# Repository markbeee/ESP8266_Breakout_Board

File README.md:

# **Breakout board for ESP8266 modules ESP-12 and ESP-07**
 
The single sided self etchable pcb is designed to power the ESP-module, has a reset and flash (program) button, the necessary pull-up/ pull-down resistors and a USB-to-serial IC (CH340G) to connect the adapter board via micro USB to the USB port on a PC. You can also wire a serial connection directly to the RX/ TX module pins.

Please bear in mind that the module pins have a 3.3 volt signal level. If you use a signal source with 5 volt (e.g. an Arduino driven by 5 volt) the RX-pin has to be driven by a voltage divider or any kind of level shifter.

The module can be connected to a power source via USB, the Vcc-pin of the module (max. 3.6 volt) or via the Vin-pins (max. 12 volt, min. 4.8 volt).

You can also connect the RTS and DTR lines via the solder bridges. If you do, you can automatically flash the module without any hassle pressing buttons. Unfortunately there are some issues with the serial output with the Arduino IDE then.

The adapter can be placed on any breadboard and leaves one row on each side available to put in jumper wires.

As the pcb is single sided you have to connect three jumper wires on the bottom (see Eagle-files for directions).

#### Parts needed (SMD)

| Part | Device                    | Value |
|------|---------------------------|-------|
| C1   | C-EUC0805                 | 22pF  |
| C2   | C-EUC0805                 | 22pF  |
| C3   | C-EUC0805                 | 100nF |
| C4   | C-EUC1206                 | 10µF  |
| C5   | C-EUC1206                 | 10µF  |
| IC1  | REG1117                   |       |
| JP1  | PINHD-1X8BIG              |       |
| JP2  | PINHD-1X8BIG              |       |
| JP3  | USB_MICROB_PLUGCONN-11752 |       |
| Q1   | CRYSTALHC49UP             | 12MHz |
| R1   | R-EU_M0805                | 4k7   |
| R2   | R-EU_M0805                | 4k7   |
| R3   | R-EU_M0805                | 4k7   |
| R4   | R-EU_M0805                | 4k7   |
| R5   | R-EU_M0805                | 1k    |
| R6   | R-EU_M0805                | 1k    |
| SJ1  | SJ                        |       |
| SJ2  | SJ                        |       |
| U$1  | ESP8266_ESP-12/ ESP-07    |       |
| U$2  | CH340G                    |       |
| U$3  | TACTILE-SWITCH-7914G      |       |
| U$4  | TACTILE-SWITCH-7914G      |       |

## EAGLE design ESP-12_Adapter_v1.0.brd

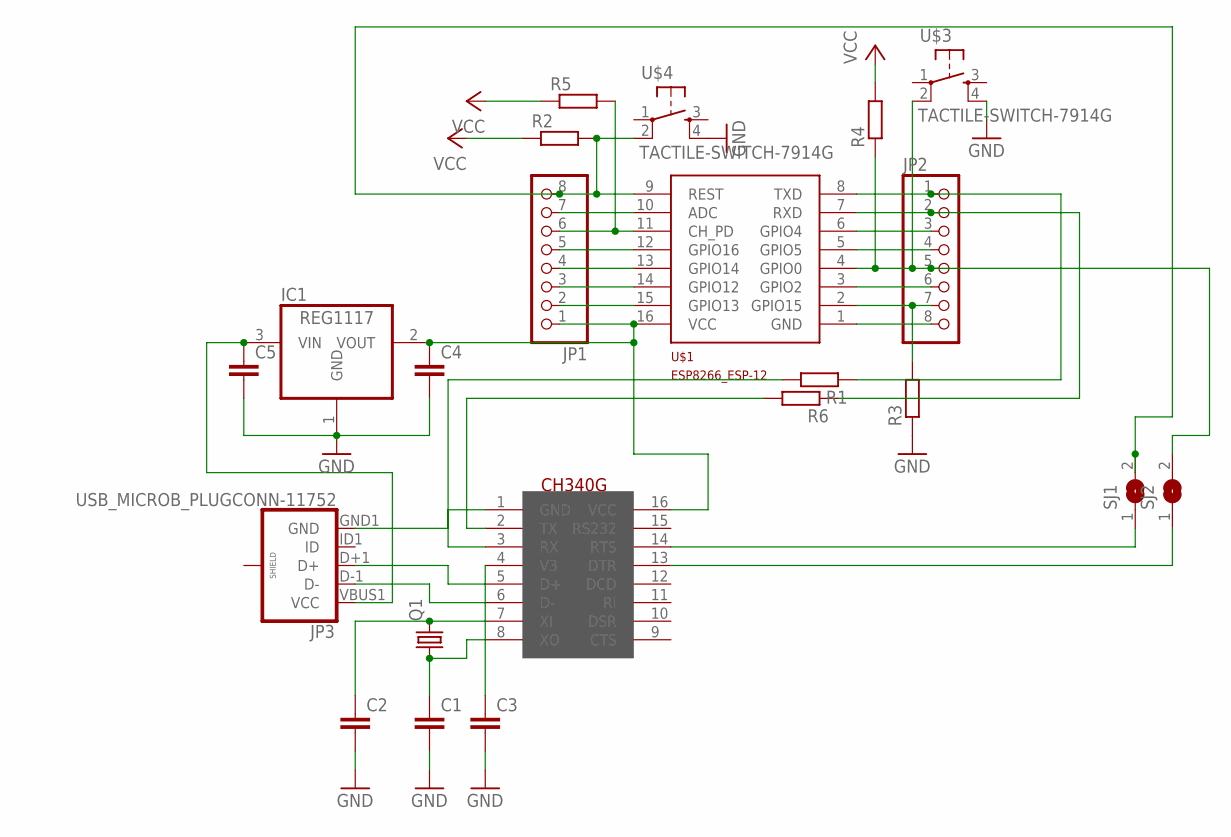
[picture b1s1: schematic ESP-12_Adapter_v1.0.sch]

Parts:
C1, C2, C3: C-EUC0805; C0805
C4, C5: C-EUC1206; C1206
IC1: REG1117; SOT223
JP1, JP2: PINHD-1X8BIG; 1X08-BIG
JP3: USB_MICROB_PLUGCONN-11752; USB-B-MICRO-SMD_V03
Q1: CRYSTALHC49UP; HC49UP
R1, R2, R3, R4, R5, R6: R-EU_M0805; M0805
SJ1, SJ2: SJ
U$1: ESP8266_ESP-12; ESP8266-ESP12
U$2: CH340G; SOIC16
U$3, U$4: TACTILE-SWITCH-7914G; 7914G

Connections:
GND: C1.2, C2.2, C3.2, C4.2, C5.2, IC1.1 (GND), JP2.8, JP3.GND1 (GND), R3.1, U$1.1 (GND), U$2.1 (GND), U$3.4, U$4.4
unnamed: JP1.8, R2.2, SJ1.2, U$1.9 (REST), U$4.2
unnamed: JP1.7, U$1.10 (ADC)
unnamed: C5.1, IC1.3 (VIN), JP3.VBUS1 (VCC)
unnamed: JP1.5, U$1.12 (GPIO16)
unnamed: JP1.4, U$1.13 (GPIO14)
unnamed: JP1.3, U$1.14 (GPIO12)
unnamed: JP1.2, U$1.15 (GPIO13)
unnamed: JP3.D+1 (D+), U$2.5 (D+)
unnamed: JP3.D-1 (D-), U$2.6 (D-)
unnamed: JP2.7, R3.2, U$1.2 (GPIO15)
unnamed: JP2.6, U$1.3 (GPIO2)
unnamed: JP2.4, U$1.5 (GPIO5)
unnamed: JP2.3, U$1.6 (GPIO4)
unnamed: JP2.1, R1.1, U$1.8 (TXD)
unnamed: R1.2, U$2.3 (RX)
unnamed: C3.1, U$2.4 (V3)
unnamed: JP1.6, R5.2, U$1.11 (CH_PD)
unnamed: C2.1, Q1.2, U$2.7 (XI)
unnamed: C1.1, Q1.1, U$2.8 (XO)
unnamed: JP2.2, R6.1, U$1.7 (RXD)
unnamed: R6.2, U$2.2 (TX)
unnamed: SJ1.1, U$2.14 (RTS)
unnamed: SJ2.1, U$2.13 (DTR)
unnamed: JP2.5, R4.1, SJ2.2, U$1.4 (GPIO0), U$3.2
VCC: C4.1, IC1.2 (VOUT), JP1.1, R2.1, R4.2, R5.1, U$1.16 (VCC), U$2.16 (VCC)

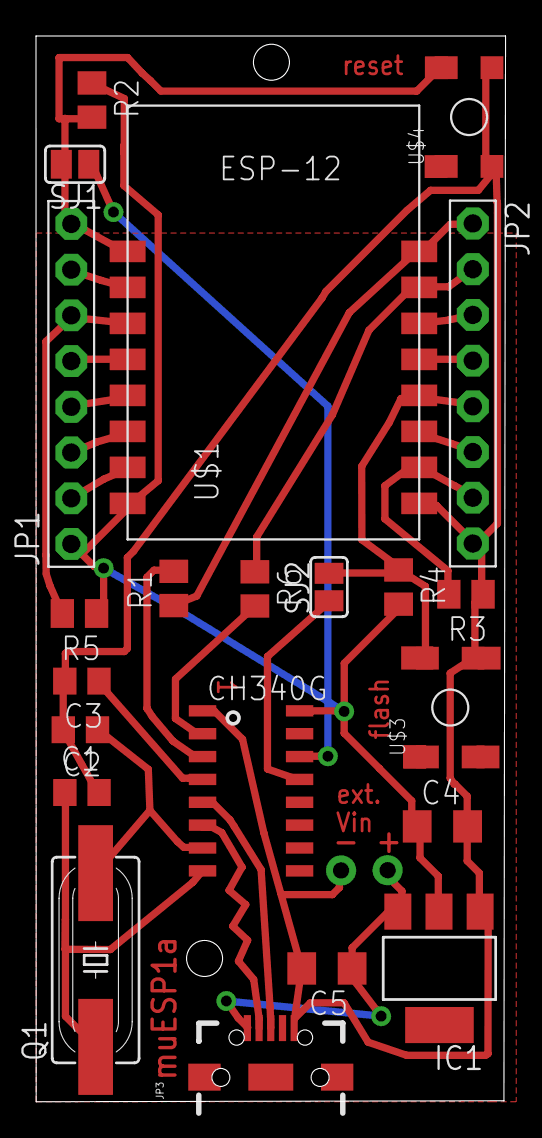
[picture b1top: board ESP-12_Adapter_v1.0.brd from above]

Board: 2 copper layers, 26.1 x 59.2 mm, 22 parts (0 on the bottom side), 26 nets.

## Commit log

2016-04-15 Initial commit for ESP8266 Breakout Board
2016-04-16 More infos on README and pictures for board/ parts
2016-04-16 corrected links to images
2016-04-18 changed image sizes
2016-04-18 added parts and values

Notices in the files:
parts and their libraries:
GeekAmmo: Licensing:Creative Commons ShareAlike 4.0 International - https://creativecommons.org/licenses/by-sa/4.0
